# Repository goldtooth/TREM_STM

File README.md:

View this project on [CADLAB.io](https://cadlab.io/project/1897). 

# TREM_STM
dfgdfg

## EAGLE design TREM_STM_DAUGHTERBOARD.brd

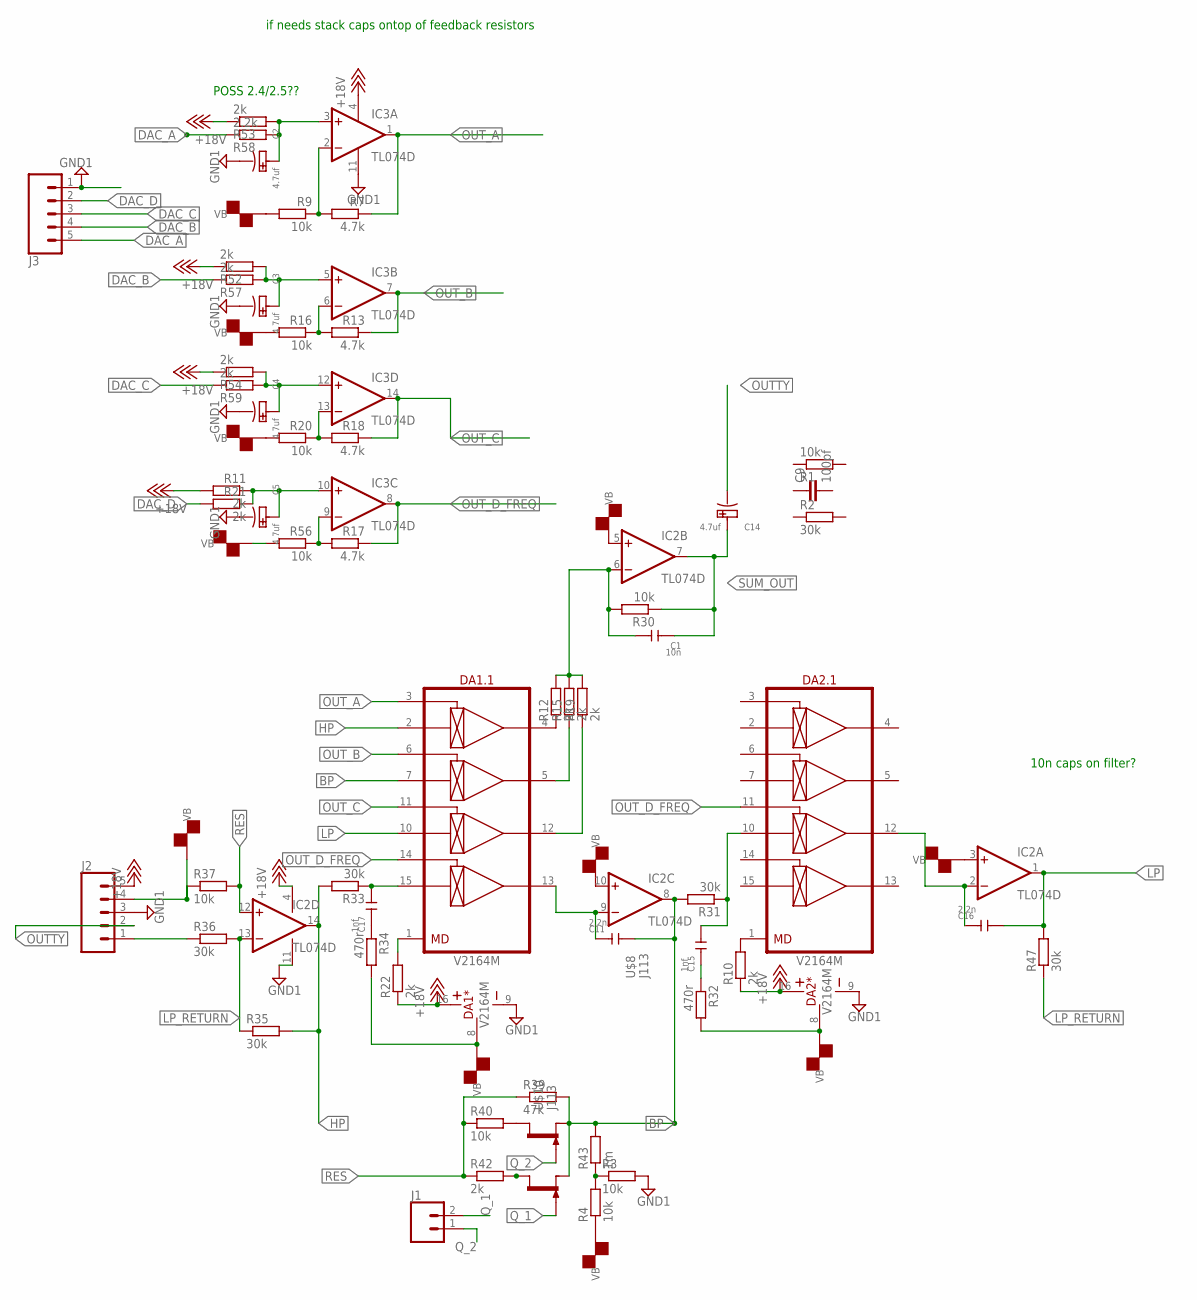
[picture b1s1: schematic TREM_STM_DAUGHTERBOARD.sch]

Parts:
C1: 10n; CERAMIC-5MM
C2, C3, C4, C5, C14: 4.7uf; PC-D5.3MM
C9: 100pf; C1206
C11, C16: 2.2n; CERAMIC-5MM
C15, C17: 1nf; CERAMIC-5MM
DA1, DA2: V2164M; SO-16
IC2, IC3: TL074D; SO14
J1: CONN_02PTH3; 1X02_LONGPADS
J2, J3: CONN_05PTH_LONGPADS; 1X05_LONGPADS
R1, R3, R4, R9, R16, R20, R30, R37, R40, R56: 10k; M1206
R2, R31, R33, R35, R36, R47: 30k; M1206
R7, R13, R17, R18: 4.7k; M1206
R10, R11, R12, R15, R19, R21, R22, R42, R52, R53, R54, R57, R59: 2k; M1206
R32, R34: 470r; M1206
R39: 47k; M1206
R43: 1m; M1206
R58: 2.2k; M1206
U$8, U$10: J113; TO92-

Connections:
+18V: DA1.16 (V+), DA2.16 (V+), IC2.4 (V+), IC3.4 (V+), J2.5, R10.1, R11.2, R22.1, R52.1, R53.1, R54.1
BP: C11.2, DA1.7 (IN2), IC2.8 (OUT), R31.2, R39.2, R43.2, U$8.2 (S), U$10.2 (S)
DAC_A: J3.5, R58.1
DAC_B: J3.4, R57.1
DAC_C: J3.3, R59.1
DAC_D: J3.2, R21.2
GND1: C2.-, C3.-, C4.-, C5.-, DA1.9 (V-), DA2.9 (V-), IC2.11 (V-), IC3.11 (V-), J2.3, J3.1, R3.2
HP: DA1.2 (IN1), IC2.14 (OUT), R33.2, R35.2
LP: C16.2, DA1.10 (IN3), IC2.1 (OUT), R47.2
LP_RETURN: IC2.13 (-IN), R35.1, R36.2, R47.1
unnamed: IC3.2 (-IN), R7.2, R9.1
unnamed: R3.1, R4.2, R43.1
unnamed: DA1.1 (MD), R22.2
unnamed: C2.+, IC3.3 (+IN), R53.2, R58.2
unnamed: C3.+, IC3.5 (+IN), R52.2, R57.2
unnamed: IC3.6 (-IN), R13.2, R16.1
unnamed: DA2.1 (MD), R10.2
unnamed: C4.+, IC3.12 (+IN), R54.2, R59.2
unnamed: C5.+, IC3.10 (+IN), R11.1, R21.1
unnamed: IC3.13 (-IN), R18.2, R20.1
unnamed: DA1.4 (OUT1), R12.1
unnamed: IC3.9 (-IN), R17.2, R56.1
unnamed: DA1.5 (OUT2), R15.1
unnamed: DA1.12 (OUT3), R19.1
unnamed: C1.2, IC2.6 (-IN), R12.2, R15.2, R19.2, R30.2
unnamed: J2.1, R36.1
unnamed: C11.1, DA1.13 (OUT4), IC2.9 (-IN)
unnamed: R40.2, U$10.3 (D)
unnamed: C15.2, DA2.10 (IN3), R31.1
unnamed: C15.1, R32.1
unnamed: C16.1, DA2.12 (OUT3), IC2.2 (-IN)
unnamed: R42.2, U$8.3 (D)
unnamed: C17.2, DA1.15 (IN4), R33.1
unnamed: C17.1, R34.1
OUTTY: C14.-, J2.2
OUT_A: DA1.3 (CV1), IC3.1 (OUT), R7.1
OUT_B: DA1.6 (CV2), IC3.7 (OUT), R13.1
OUT_C: DA1.11 (CV3), IC3.14 (OUT), R18.1
OUT_D_FREQ: DA1.14 (CV4), DA2.11 (CV3), IC3.8 (OUT), R17.1
Q_1: J1.2, U$8.1 (G)
Q_2: J1.1, U$10.1 (G)
RES: IC2.12 (+IN), R37.2, R39.1, R40.1, R42.1
SUM_OUT: C1.1, C14.+, IC2.7 (OUT), R30.1
VB: DA1.8 (GND), DA2.8 (GND), IC2.3 (+IN), IC2.5 (+IN), IC2.10 (+IN), J2.4, R4.1, R9.2, R16.2, R20.2, R32.2, R34.2, R37.1, R56.2

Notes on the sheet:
if needs stack caps ontop of feedback resistors
POSS 2.4/2.5??
10n caps on filter?

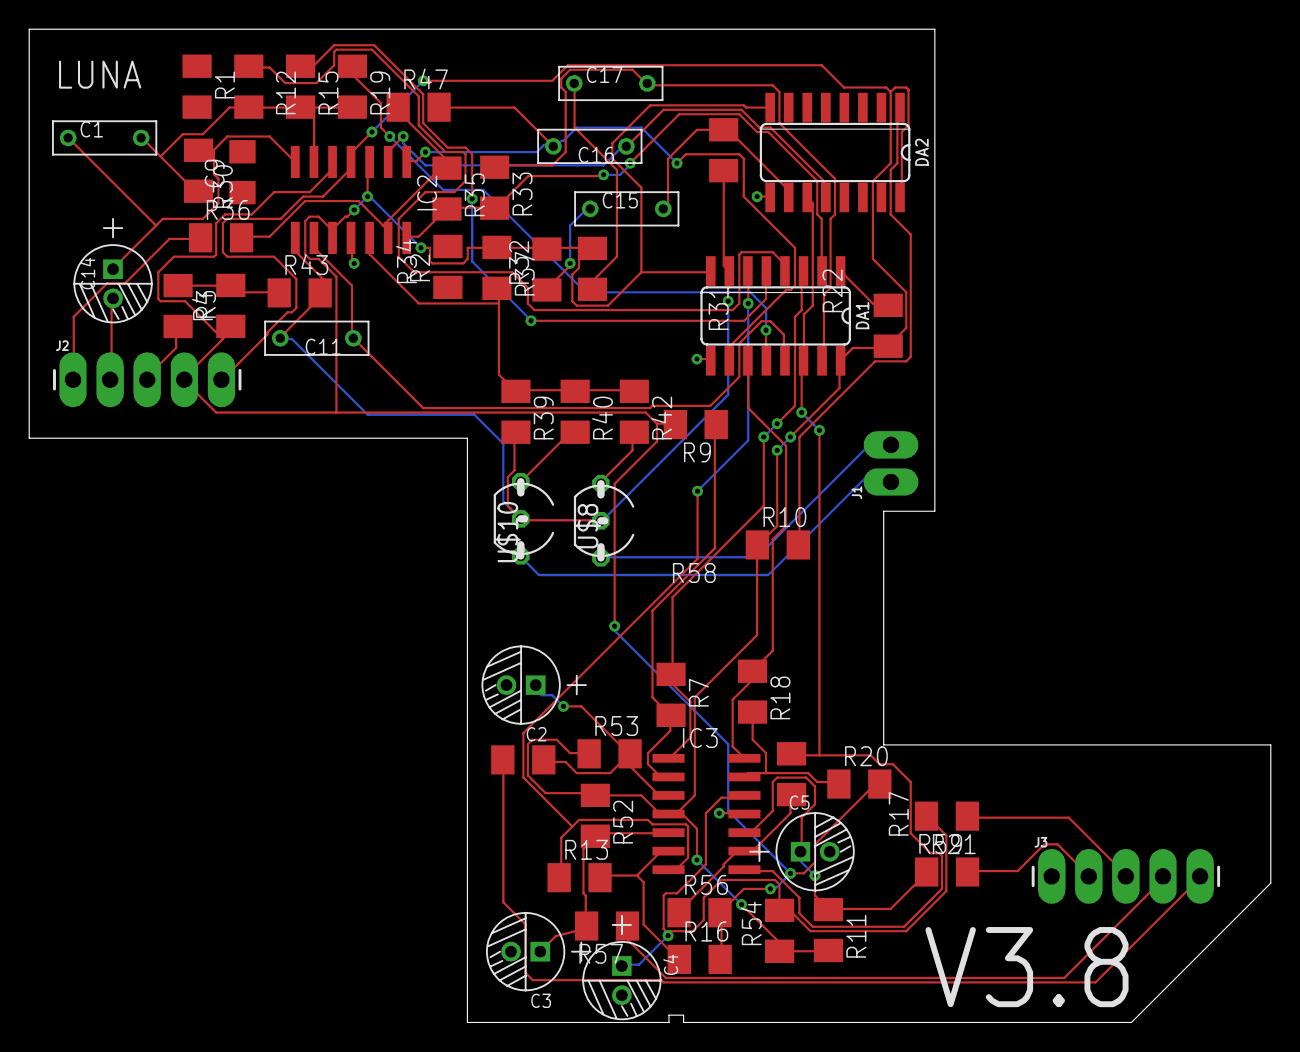
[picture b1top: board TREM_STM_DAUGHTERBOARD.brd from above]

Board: 2 copper layers, 85.0 x 68.0 mm, 58 parts (0 on the bottom side), 44 nets.

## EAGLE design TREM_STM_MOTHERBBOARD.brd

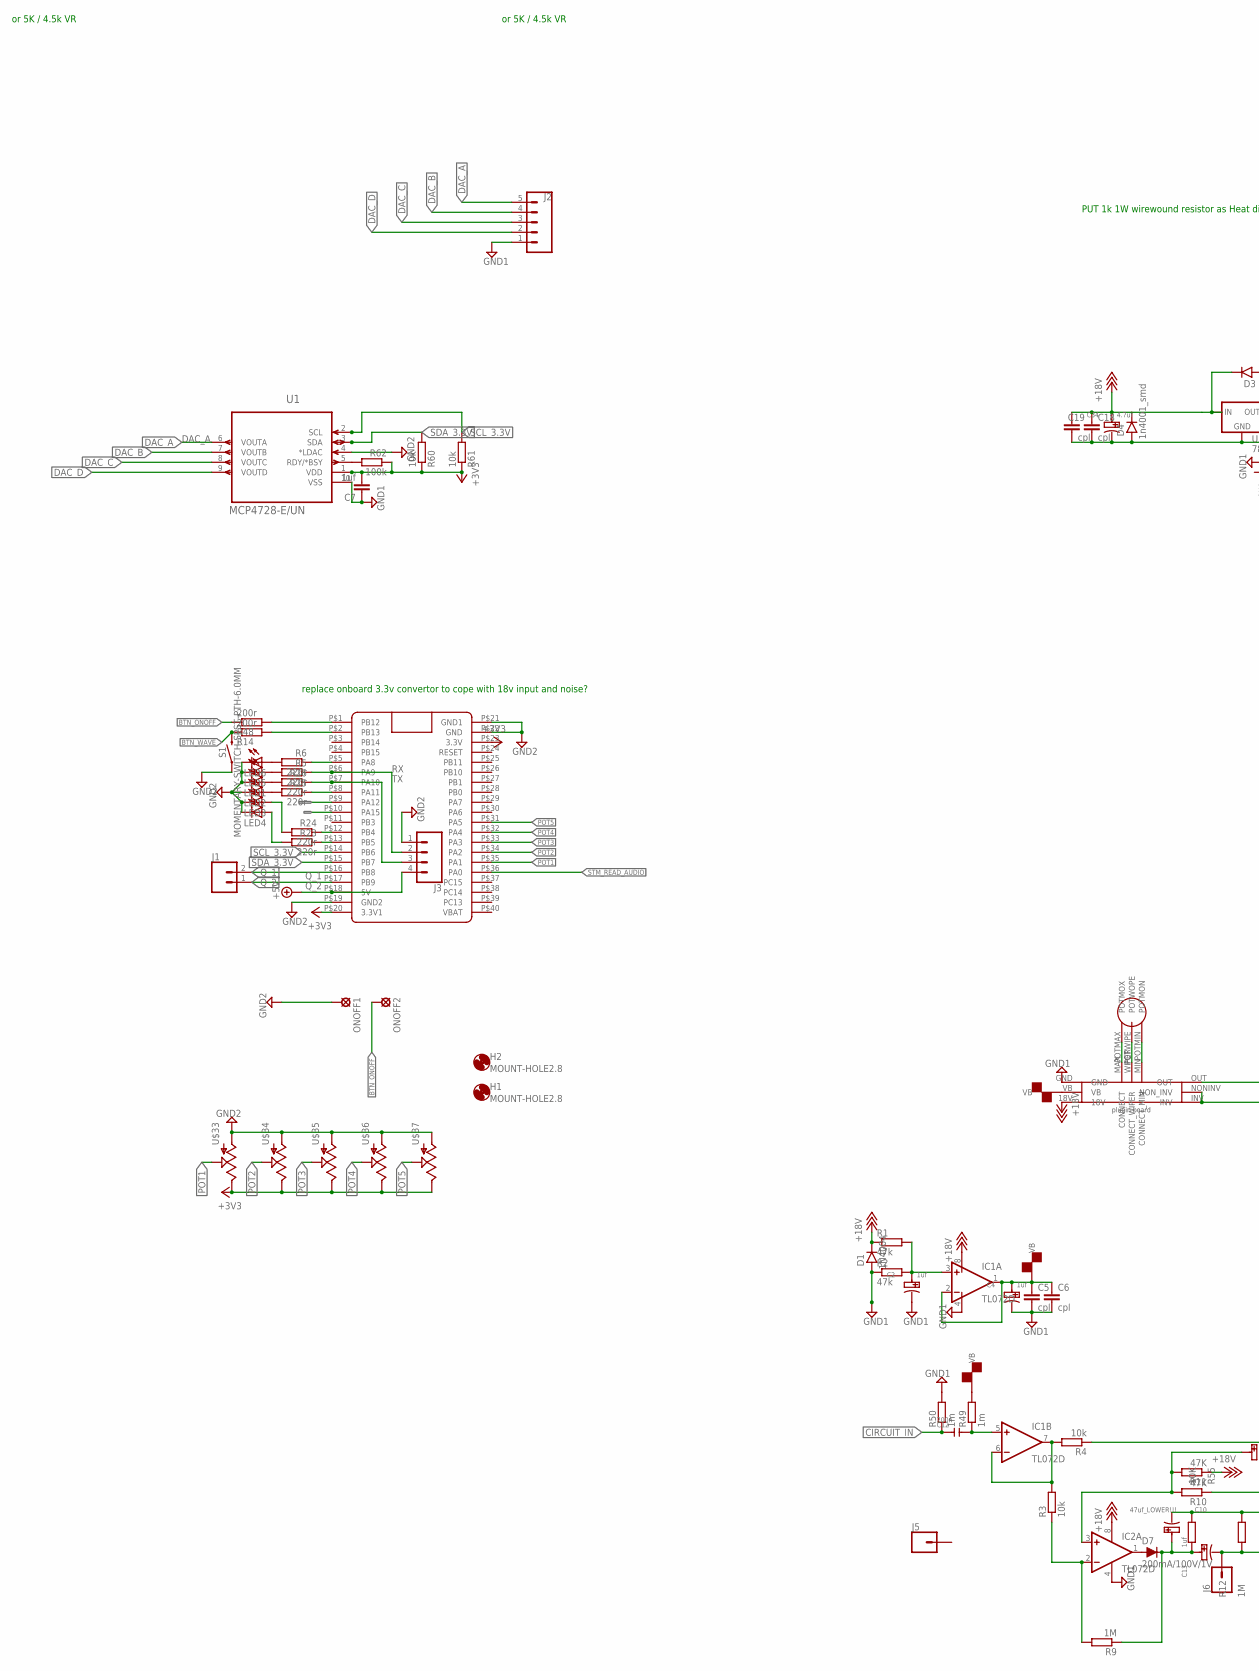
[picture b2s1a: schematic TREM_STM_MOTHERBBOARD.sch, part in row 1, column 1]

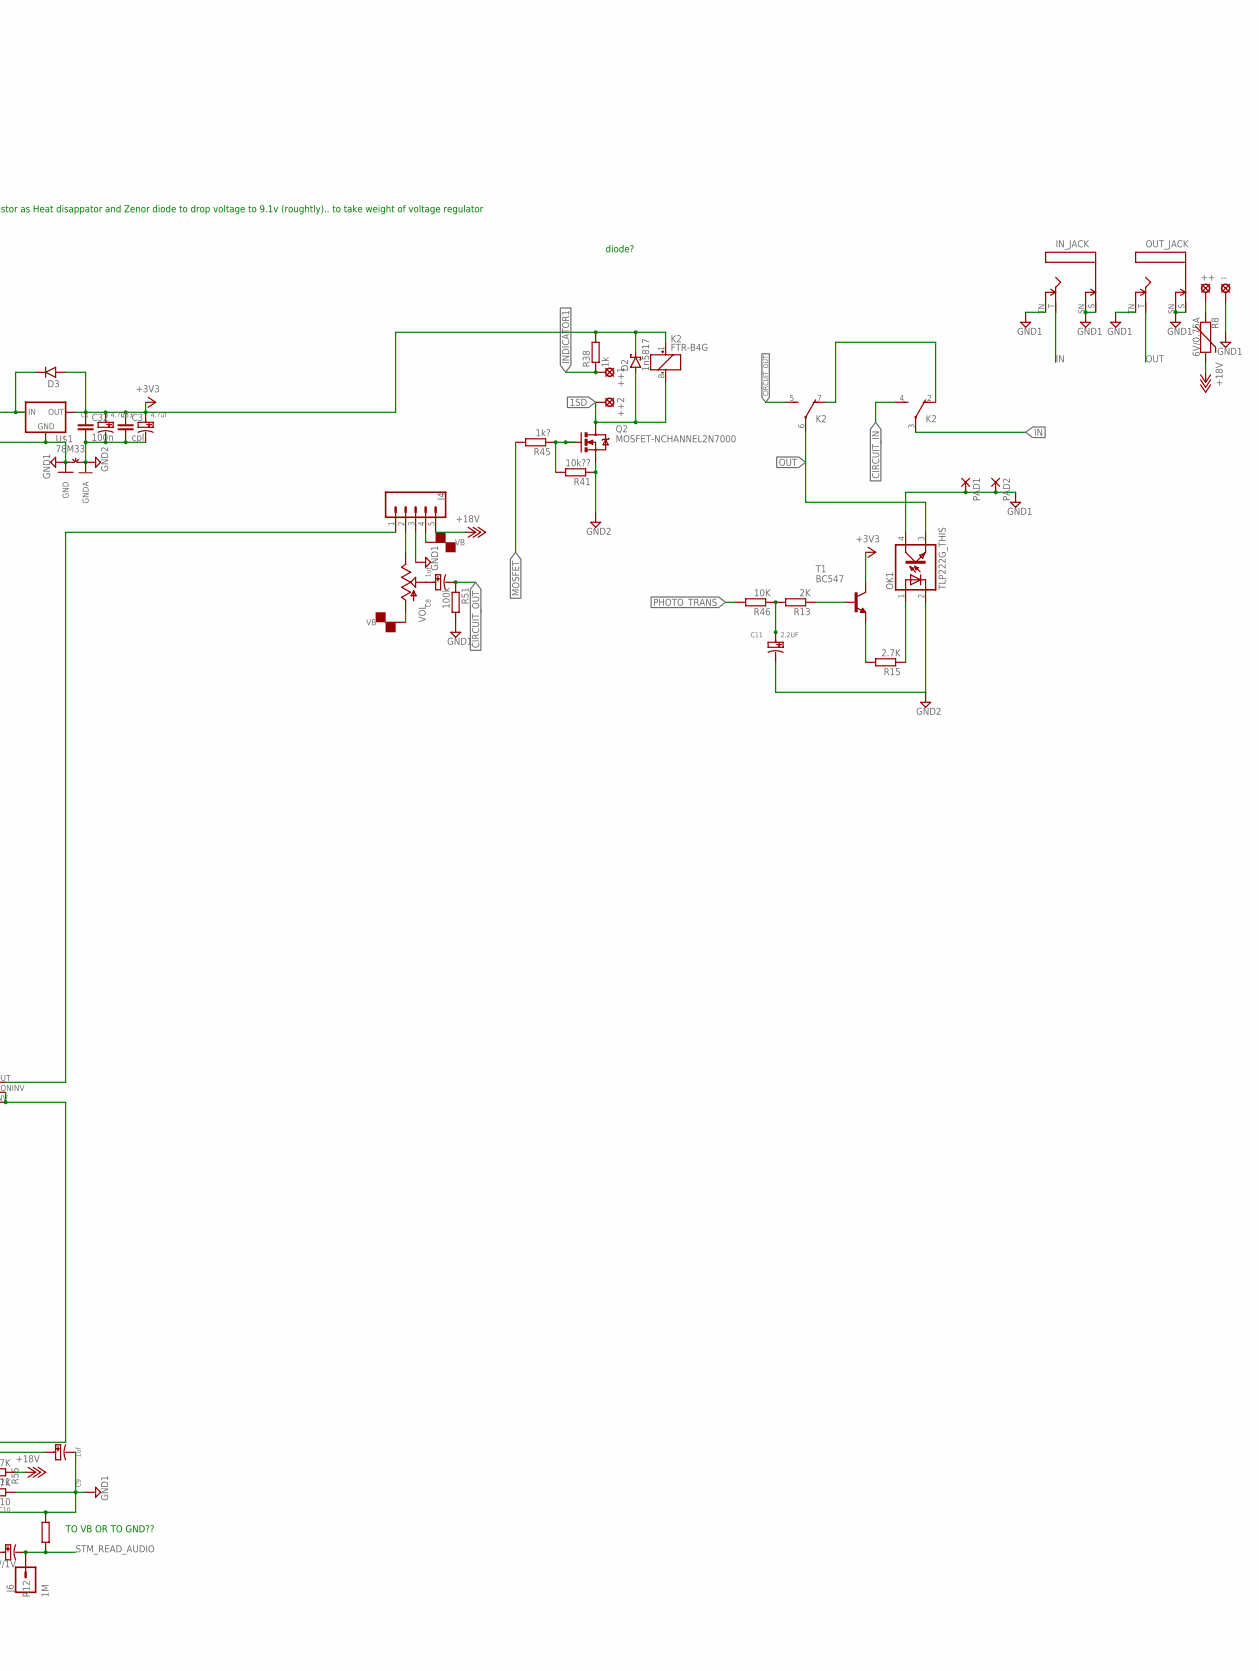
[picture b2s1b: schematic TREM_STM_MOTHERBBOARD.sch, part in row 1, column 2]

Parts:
++, ++1, ++2: LSP10
--: LSP10
C1, C33, C34: 4.7uf; PC-D5.3MM
C2, C4, C8, C9, C13: 1uf; PC-D5.3MM
C3, C5, C6, C18, C19: cpl; C1206
C7: 1uf; C1206
C10: 47uf_LOWER!!!; PC-D5.3MM
C11: 2.2UF; PC-D5.3MM
C12: 200n; CERAMIC-5MM
C32: 100n; C1206
D1: 1N4004; DO41-1
D2: 1n5817; SMB
D3, D4: 1n4001_smd; DO41-1
D7: 200mA/100V/1V; DIODE-1N4148
H1, H2: MOUNT-HOLE2.8; 2,8
IC1, IC2: TL072D; SO08
IN_JACK: MMMONNNNOHOLES; MONONOHOLES
J1: CONN_02PTH3; 1X02_LONGPADS
J2, J4: CONN_05PTH_LONGPADS; 1X05_LONGPADS
J3: CONN_04LONGPADS; 1X04_LONGPADS
J5, J6: CONN_01; 1X01
K2: FTR-B4G
LED1, LED2, LED3, LED4, LED5, LED6: LED3MM
OK1: TLP222G_THIS; DIL04
ONOFF1, ONOFF2: LSP10
OUT_JACK: MMMONNNNOHOLES; MONONOHOLES
PAD1, PAD2: SMD2; SMD1,27-2,54
Q2: MOSFET-NCHANNEL2N7000; TO-92
R1, R2: 47k; M1206
R3, R4, R60, R61: 10k; M1206
R5, R6, R23, R24, R25, R26: 220r; M1206
R8: 6V/0.75A; 1206
R9, R12: 1M; M1206
R10, R11: 47K; M1206
R13: 2K; M1206
R14, R48: 200r; M1206
R15: 2.7K; M1206
R38: 1k; M1206
R41: 10k??; M1206
R45: 1k?; M1206
R46, R55: 10K; M1206
R49, R50: 1m; M1206
R51, R62: 100k; M1206
S1: MOMENTARY-SWITCH-SPST-PTH-6.0MM; TACTILE_SWITCH_PTH_6.0MM
T1: BC547; TO92
U1: MCP4728-E/UN; SOP50P490X110-10N
U$1: 78M33; SOT223
U$4: GT_PLUGIN; PLUGIN_RECIEVE
U$11: BLUE_PILL
U$33, U$34, U$35, U$36, U$37: POT; ALPS_POT
VOL: POT; ALPS_POT
~NUDEV~1: GND-GNDA1,27MM; GND-GNDA-1,27MM

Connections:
1SD: ++2.MP, D2.A, K2.8 (-), Q2.3 (D)
+3V3: C1.+, C3.1, C7.2, C32.1, C33.+, D2.C, D3.A, K2.1 (+), R38.2, R60.1, R61.1, R62.1, T1.3 (C), U1.1 (VDD), U$1.3 (OUT), U$11.P$20 (3.3V1), U$11.P$23 (3.3V), U$33.P$1 (E), U$34.P$1 (E), U$35.P$1 (E), U$36.P$1 (E), U$37.P$1 (E)
+5V: J3.4, U$11.P$18 (5V)
+18V: D1.C, IC1.8 (V+), IC2.8 (V+), J4.5, R1.1, R8.2, R11.1, U$4.18V
BTN_ONOFF: ONOFF2.MP, R48.1
BTN_WAVE: R14.1, S1.3 (2)
CIRCUIT_IN: C12.1, K2.4 (S), R50.1
CIRCUIT_OUT: C8.-, K2.5 (S), R51.1
DAC_A: J2.5, U1.6 (VOUTA)
DAC_B: J2.4, U1.7 (VOUTB)
DAC_C: J2.3, U1.8 (VOUTC)
DAC_D: J2.2, U1.9 (VOUTD)
GND1: --.MP, C2.-, C4.-, C5.2, C6.2, C7.1, C9.-, C10.-, C18.2, C19.2, C34.-, D1.A, D4.A, IC1.4 (V-), IC2.4 (V-), IN_JACK.S, IN_JACK.SN, IN_JACK.TN, J2.1, J4.3, OK1.4 (COL), OUT_JACK.S, OUT_JACK.SN, OUT_JACK.TN, PAD1.1, PAD2.1, R2.1, R10.1, R12.2, R50.2, R51.2, R55.1, U1.10 (VSS), U$1.2 (GND), U$1.4 (GND), U$4.GND, ~NUDEV~1.GND
GND2: C1.-, C3.2, C11.-, C32.2, C33.-, J3.1, LED1.K (C), LED2.K (C), LED3.K (C), LED4.K (C), LED5.K (C), LED6.K (C), OK1.2 (C), ONOFF1.MP, Q2.1 (S), R41.1, S1.1, U1.4 (*LDAC), U$11.P$19 (GND2), U$11.P$21 (GND1), U$11.P$22 (GND), U$33.P$3 (A), U$34.P$3 (A), U$35.P$3 (A), U$36.P$3 (A), U$37.P$3 (A), ~NUDEV~1.GNDA
IN: IN_JACK.T, K2.3
INDICATOR1: ++1.MP, R38.1
MOSFET: R45.2, U$11.P$10 (PA15)
unnamed: J4.1, U$4.OUT
unnamed: C2.+, IC1.3 (+IN), R1.2, R2.2
unnamed: U$4.MAX (CONNECT), U$4.POTMAX (POTMOX)
unnamed: U$4.POTWIPE (POTWOPE), U$4.WIPER (CONNECT_WIPER)
unnamed: U$4.MIN (CONNECT_MIN), U$4.POTMIN (POTMON)
unnamed: R4.1, U$4.INV, U$4.NONINV (NON_INV)
unnamed: R23.1, U$11.P$13 (PB5)
unnamed: R24.1, U$11.P$12 (PB4)
unnamed: C9.+, IC2.3 (+IN), R10.2, R11.2
unnamed: C8.+, VOL.P$2 (S)
unnamed: C18.1, C19.1, C34.+, D3.C, D4.C, U$1.1 (IN)
unnamed: R62.2, U1.5 (RDY/*BSY)
unnamed: C10.+, C13.+, D7.C, R9.1, R55.2
unnamed: IC2.2 (-IN), R3.1, R9.2
unnamed: C11.+, R13.2, R46.1
unnamed: IC1.6 (-IN), IC1.7 (OUT), R3.2, R4.2
unnamed: D7.A, IC2.1 (OUT)
unnamed: R15.2, T1.1 (E)
unnamed: R25.1, U$11.P$8 (PA11)
unnamed: OK1.1 (A), R15.1
unnamed: R13.1, T1.2 (B)
unnamed: LED1.A, R26.2
unnamed: LED2.A, R25.2
unnamed: K2.2 (O), K2.7 (O)
unnamed: LED3.A, R24.2
unnamed: LED4.A, R23.2
unnamed: J4.2, VOL.P$1 (E)
unnamed: ++.MP, R8.1
unnamed: C12.2, IC1.5 (+IN), R49.1
unnamed: R48.2, U$11.P$1 (PB12)
unnamed: R14.2, U$11.P$2 (PB13)
unnamed: R6.1, U$11.P$5 (PA8)
unnamed: LED5.A, R5.2
unnamed: LED6.A, R6.2
unnamed: Q2.2 (G), R41.2, R45.1
OUT: K2.6, OK1.3 (EMIT), OUT_JACK.T
PHOTO_TRANS: R46.2, U$11.P$9 (PA12)
POT1: U$11.P$35 (PA1), U$33.P$2 (S)
POT2: U$11.P$34 (PA2), U$34.P$2 (S)
POT3: U$11.P$33 (PA3), U$35.P$2 (S)
POT4: U$11.P$32 (PA4), U$36.P$2 (S)
POT5: U$11.P$31 (PA5), U$37.P$2 (S)
Q_1: J1.2, U$11.P$16 (PB8)
Q_2: J1.1, U$11.P$17 (PB9)
RX: J3.2, R5.1, U$11.P$6 (PA9)
SCL_3.3V: R61.2, U1.2 (SCL), U$11.P$14 (PB6)
SDA_3.3V: R60.2, U1.3 (SDA), U$11.P$15 (PB7)
STM_READ_AUDIO: C13.-, J6.1, R12.1, U$11.P$36 (PA0)
TX: J3.3, R26.1, U$11.P$7 (PA10)
VB: C4.+, C5.1, C6.1, IC1.1 (OUT), IC1.2 (-IN), J4.4, R49.2, U$4.VB, VOL.P$3 (A)

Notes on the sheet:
diode?
replace onboard 3.3v convertor to cope with 18v input and noise?
or 5K / 4.5k VR
PUT 1k 1W wirewound resistor as Heat disappator and Zenor diode to drop voltage to 9.1v (roughtly).. to take weight of voltage regulator
TO VB OR TO GND??

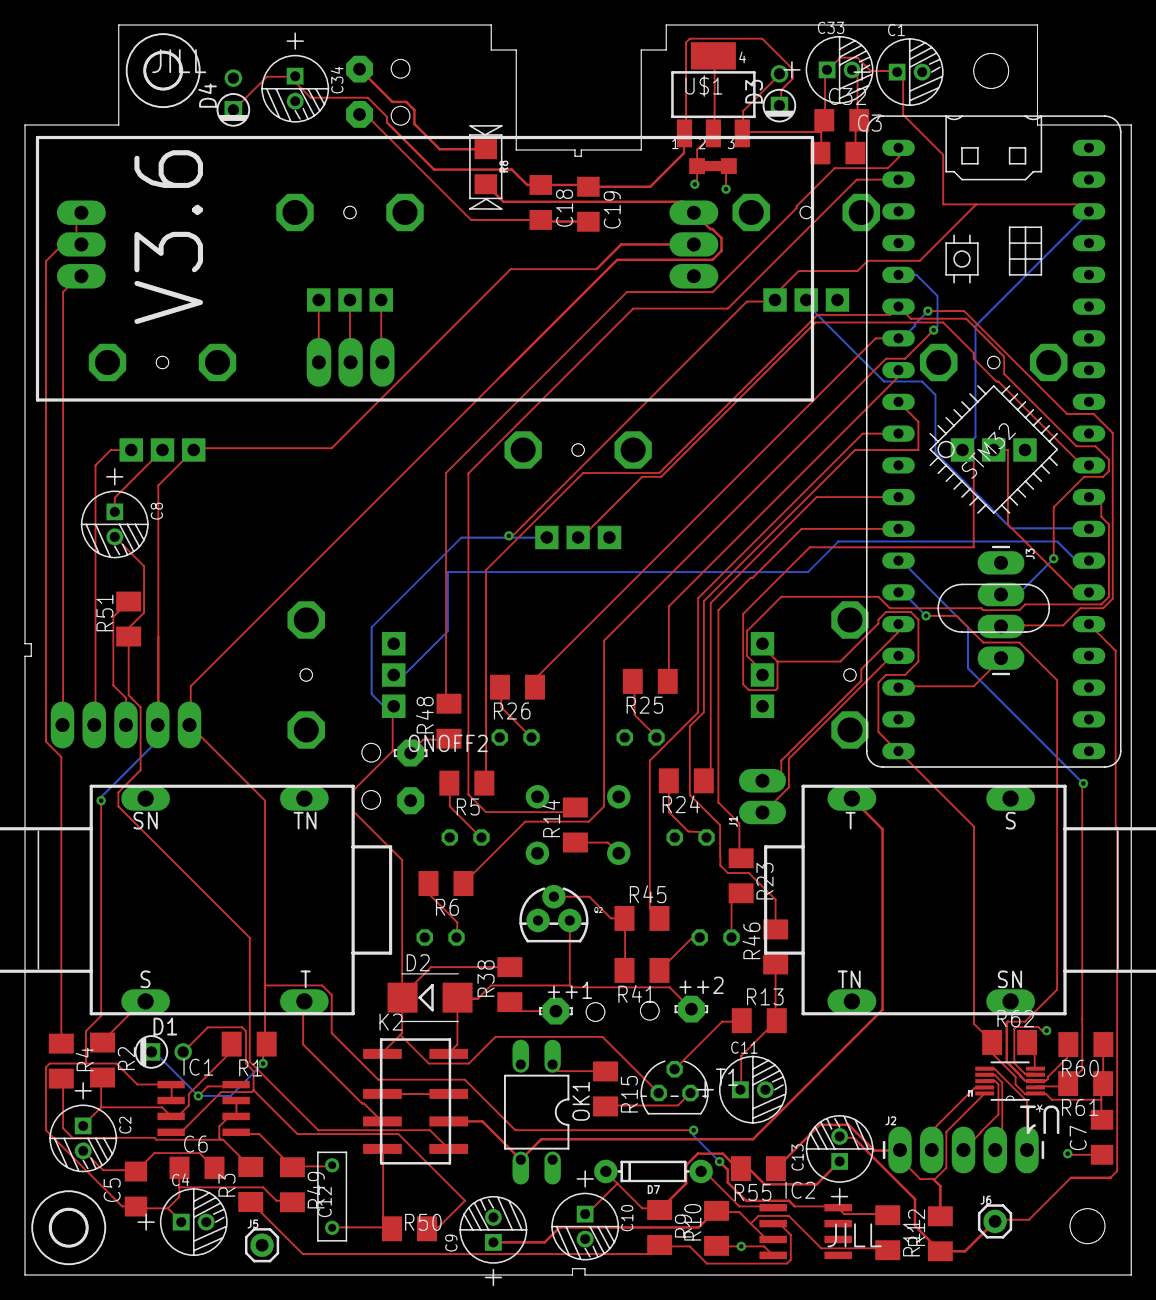
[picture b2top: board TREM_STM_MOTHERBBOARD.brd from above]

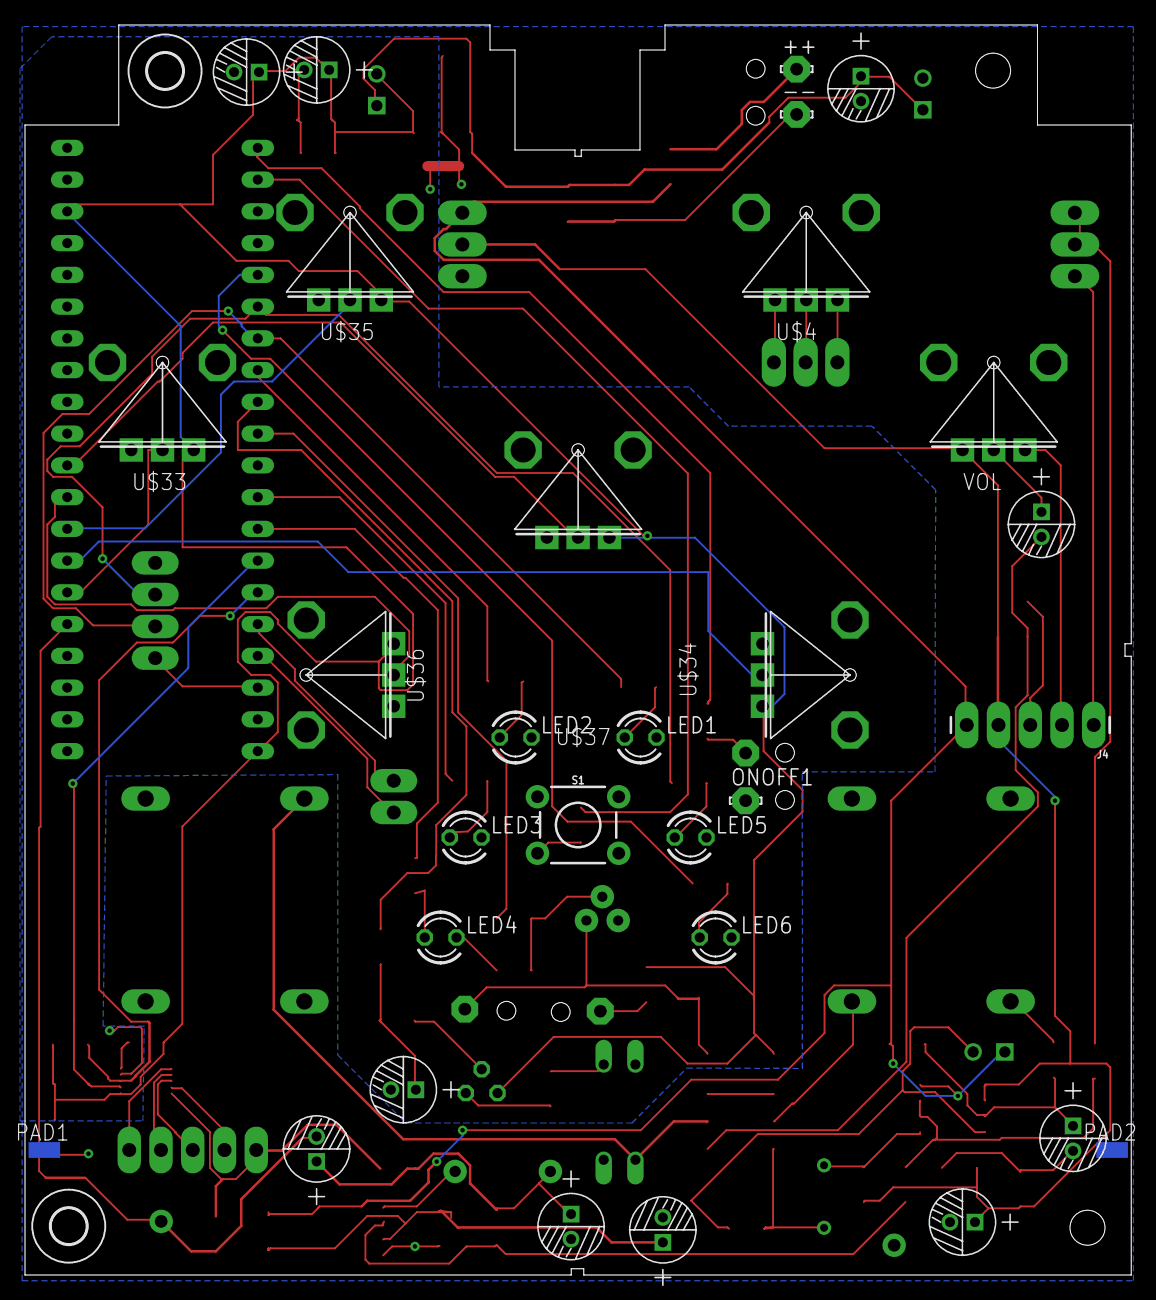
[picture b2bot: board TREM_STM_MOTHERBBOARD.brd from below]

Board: 2 copper layers, 88.5 x 100.0 mm, 103 parts (15 on the bottom side), 67 nets.

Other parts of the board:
H3, H4: MOUNT-HOLE2.8; 2,8
U$2, U$3, U$5, U$9, U$12, U$13: HOLD

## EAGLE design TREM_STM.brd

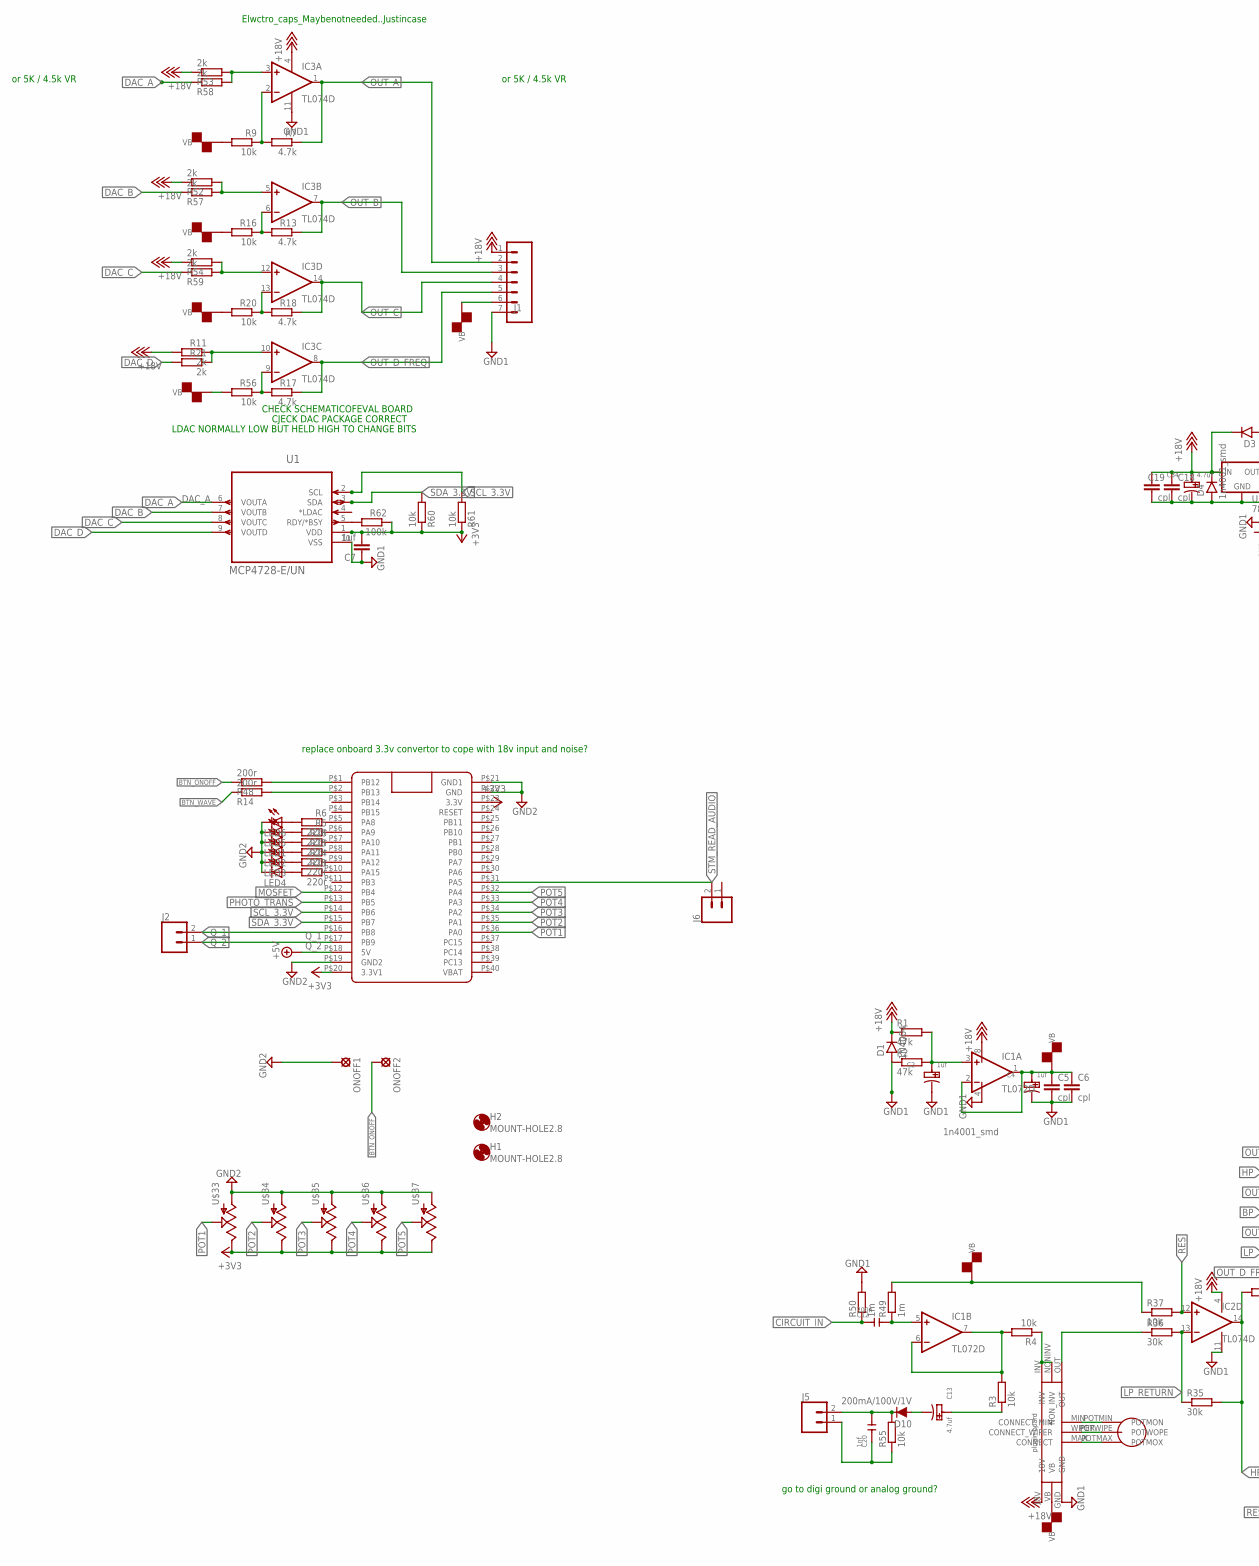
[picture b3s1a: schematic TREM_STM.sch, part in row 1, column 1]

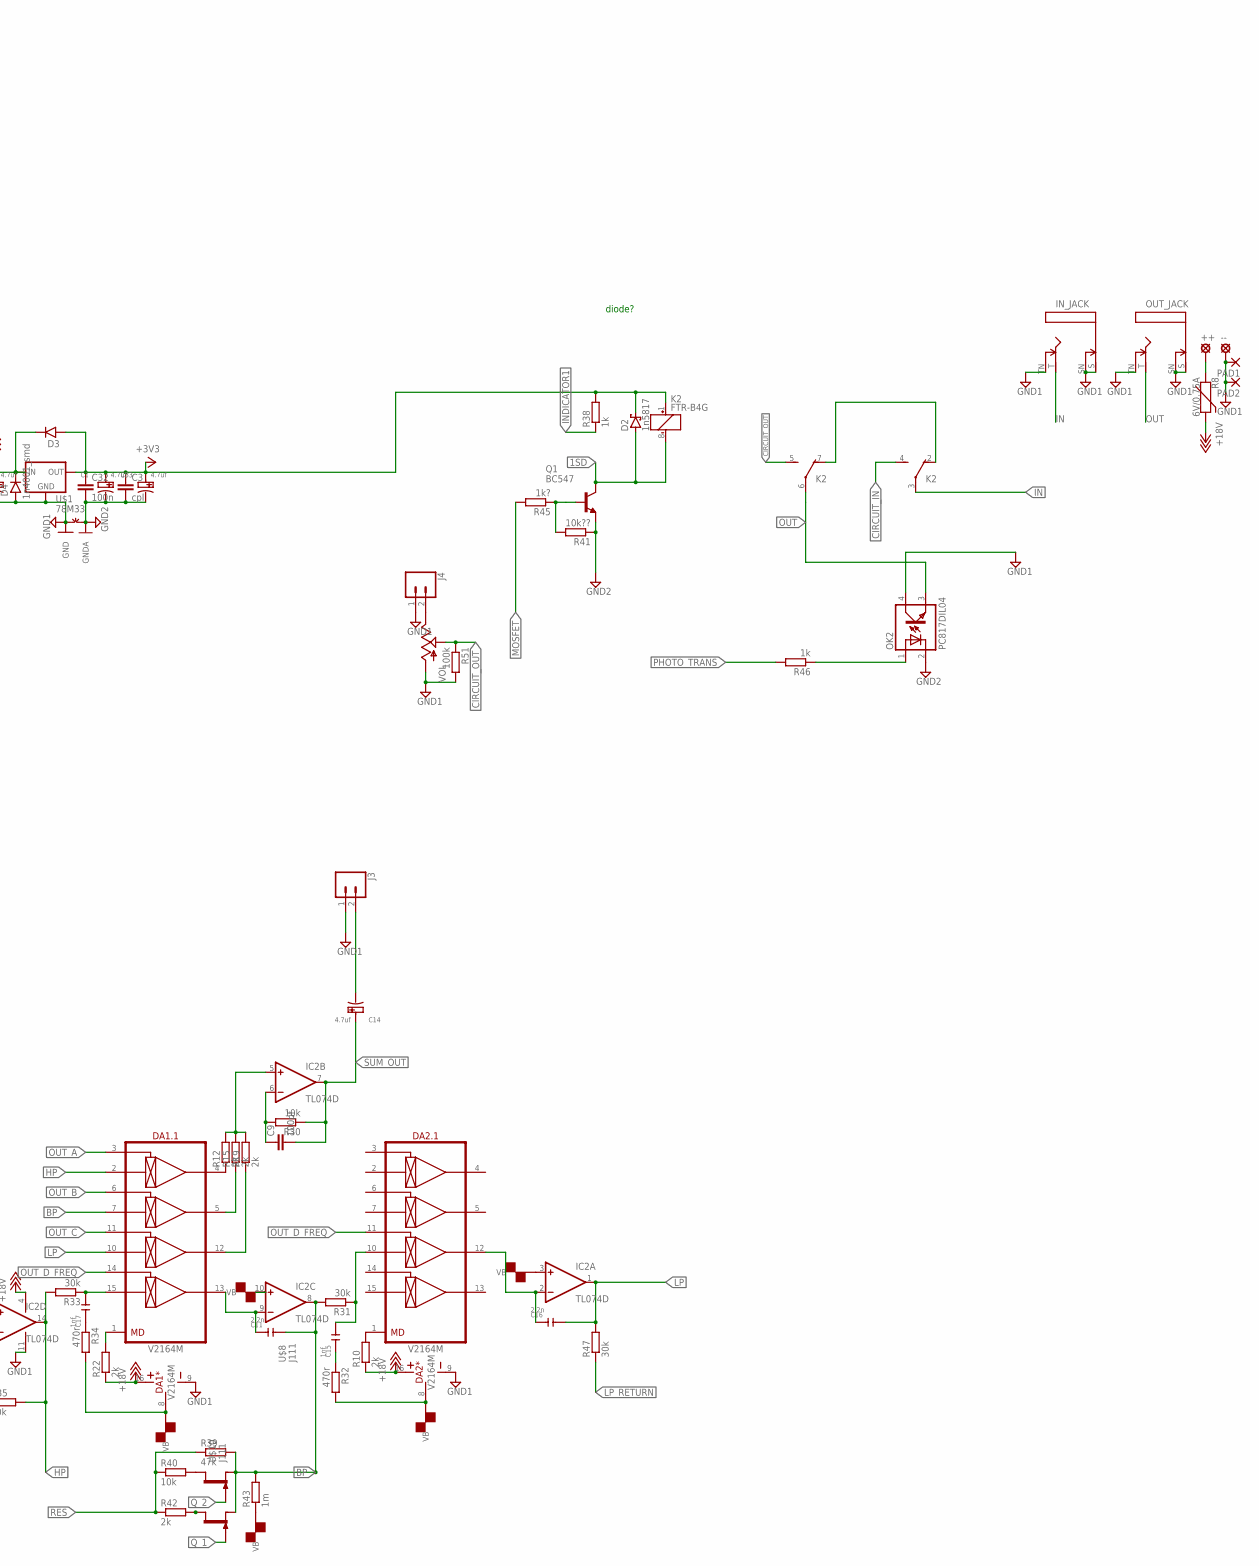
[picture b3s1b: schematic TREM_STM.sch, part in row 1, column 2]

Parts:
++: LSP10
--: LSP10
C1, C13, C14, C33, C34: 4.7uf; PC-D5.3MM
C2, C4: 1uf; PC-D5.3MM
C3, C5, C6, C18, C19: cpl; C1206
C7: 1uf; C1206
C9: 100pf; C1206
C11, C16: 2.2n; CERAMIC-5MM
C12: 200n; CERAMIC-5MM
C15, C17, C20: 1nf; CERAMIC-5MM
C32: 100n; C1206
D1: 1N4004; DO41-1
D2: 1n5817; SMB
D3, D4: 1n4001_smd; DO41-1
D10: 200mA/100V/1V; DIODE-1N4148
DA1, DA2: V2164M; SO-16
H1, H2: MOUNT-HOLE2.8; 2,8
IC1: TL072D; SO08
IC2, IC3: TL074D; SO14
IN_JACK: MMMONNNNOHOLES; MONONOHOLES
J1: CONN_07LONGPADS; 1X07_LONGPADS
J2, J3, J4, J5, J6: CONN_02PTH3; 1X02_LONGPADS
K2: FTR-B4G
LED1, LED2, LED3, LED4, LED5, LED6: LED3MM
OK2: PC817DIL04; SMD4
ONOFF1, ONOFF2: LSP10
OUT_JACK: MMMONNNNOHOLES; MONONOHOLES
PAD1, PAD2: SMD5; SMD2,54-5,08
Q1: BC547; TO92
R1, R2, R39: 47k; M1206
R3, R4, R9, R16, R20, R30, R37, R40, R55, R56, R60, R61: 10k; M1206
R5, R6, R23, R24, R25, R26: 220r; M1206
R7, R13, R17, R18: 4.7k; M1206
R8: 6V/0.75A; 1206
R10, R11, R12, R15, R19, R21, R22, R42, R52, R53, R54, R57, R58, R59: 2k; M1206
R14, R48: 200r; M1206
R31, R33, R35, R36, R47: 30k; M1206
R32, R34: 470r; M1206
R38, R46: 1k; M1206
R41: 10k??; M1206
R43, R49, R50: 1m; M1206
R45: 1k?; M1206
R51, R62: 100k; M1206
U1: MCP4728-E/UN; SOP50P490X110-10N
U$1: 78M33; SOT223
U$8, U$10: J111; TO92-
U$11: BLUE_PILL
U$32: GT_PLUGIN; PLUGIN_RECIEVE
U$33, U$34, U$35, U$36, U$37: POT; ALPS_POT
VOL: POT; ALPS_POT
~NUDEV~1: GND-GNDA1,27MM; GND-GNDA-1,27MM

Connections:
1SD: D2.A, K2.8 (-), Q1.3 (C)
+3V3: C1.+, C3.1, C7.2, C32.1, C33.+, D2.C, D3.A, K2.1 (+), R38.2, R60.1, R61.1, R62.1, U1.1 (VDD), U$1.3 (OUT), U$11.P$20 (3.3V1), U$11.P$23 (3.3V), U$33.P$1 (E), U$34.P$1 (E), U$35.P$1 (E), U$36.P$1 (E), U$37.P$1 (E)
+5V: U$11.P$18 (5V)
+18V: C18.1, C19.1, C34.+, D1.C, D3.C, D4.C, DA1.16 (V+), DA2.16 (V+), IC1.8 (V+), IC2.4 (V+), IC3.4 (V+), J1.1, R1.1, R8.2, R10.1, R11.2, R22.1, R52.1, R53.1, R54.1, U$1.1 (IN), U$32.18V
BP: C11.2, DA1.7 (IN2), IC2.8 (OUT), R31.2, R39.2, R43.2, U$8.2 (S), U$10.2 (S)
BTN_ONOFF: ONOFF2.MP, R48.1
BTN_WAVE: R14.1
CIRCUIT_IN: C12.1, K2.4 (S), R50.1
CIRCUIT_OUT: K2.5 (S), R51.1, VOL.P$2 (S)
DAC_A: R58.1, U1.6 (VOUTA)
DAC_B: R57.1, U1.7 (VOUTB)
DAC_C: R59.1, U1.8 (VOUTC)
DAC_D: R21.2, U1.9 (VOUTD)
GND1: --.MP, C2.-, C4.-, C5.2, C6.2, C7.1, C18.2, C19.2, C34.-, D1.A, D4.A, DA1.9 (V-), DA2.9 (V-), IC1.4 (V-), IC2.11 (V-), IC3.11 (V-), IN_JACK.S, IN_JACK.SN, IN_JACK.TN, J1.7, J3.1, J4.1, OK2.4 (COL), OUT_JACK.S, OUT_JACK.SN, OUT_JACK.TN, PAD1.1, PAD2.1, R2.1, R50.2, U1.10 (VSS), U$1.2 (GND), U$1.4 (GND), U$32.GND, ~NUDEV~1.GND
GND2: C1.-, C3.2, C32.2, C33.-, LED1.K (C), LED2.K (C), LED3.K (C), LED4.K (C), LED5.K (C), LED6.K (C), OK2.2 (C), ONOFF1.MP, Q1.1 (E), R41.1, U$11.P$19 (GND2), U$11.P$21 (GND1), U$11.P$22 (GND), U$33.P$3 (A), U$34.P$3 (A), U$35.P$3 (A), U$36.P$3 (A), U$37.P$3 (A), ~NUDEV~1.GNDA
HP: DA1.2 (IN1), IC2.14 (OUT), R33.2, R35.2
IN: IN_JACK.T, K2.3
INDICATOR1: R38.1
LP: C16.2, DA1.10 (IN3), IC2.1 (OUT), R47.2
LP_RETURN: IC2.13 (-IN), R35.1, R36.2, R47.1
MOSFET: R45.2, U$11.P$12 (PB4)
unnamed: IC3.2 (-IN), R7.2, R9.1
unnamed: C2.+, IC1.3 (+IN), R1.2, R2.2
unnamed: DA1.1 (MD), R22.2
unnamed: IC3.3 (+IN), R53.2, R58.2
unnamed: IC3.5 (+IN), R52.2, R57.2
unnamed: IC3.6 (-IN), R13.2, R16.1
unnamed: DA2.1 (MD), R10.2
unnamed: IC3.12 (+IN), R54.2, R59.2
unnamed: IC3.10 (+IN), R11.1, R21.1
unnamed: IC3.13 (-IN), R18.2, R20.1
unnamed: DA1.4 (OUT1), R12.1
unnamed: R62.2, U1.5 (RDY/*BSY)
unnamed: IC3.9 (-IN), R17.2, R56.1
unnamed: DA1.5 (OUT2), R15.1
unnamed: DA1.12 (OUT3), R19.1
unnamed: IC1.6 (-IN), IC1.7 (OUT), R3.2, R4.2
unnamed: R23.1, U$11.P$10 (PA15)
unnamed: R24.1, U$11.P$9 (PA12)
unnamed: R25.1, U$11.P$8 (PA11)
unnamed: IC2.5 (+IN), R12.2, R15.2, R19.2
unnamed: C9.1, IC2.6 (-IN), R30.2
unnamed: R26.1, U$11.P$7 (PA10)
unnamed: R36.1, U$32.OUT
unnamed: C11.1, DA1.13 (OUT4), IC2.9 (-IN)
unnamed: R40.2, U$10.3 (D)
unnamed: C15.2, DA2.10 (IN3), R31.1
unnamed: C15.1, R32.1
unnamed: C16.1, DA2.12 (OUT3), IC2.2 (-IN)
unnamed: R42.2, U$8.3 (D)
unnamed: C17.2, DA1.15 (IN4), R33.1
unnamed: LED1.A, R26.2
unnamed: R4.1, U$32.INV, U$32.NONINV (NON_INV)
unnamed: U$32.MIN (CONNECT_MIN), U$32.POTMIN (POTMON)
unnamed: U$32.POTWIPE (POTWOPE), U$32.WIPER (CONNECT_WIPER)
unnamed: U$32.MAX (CONNECT), U$32.POTMAX (POTMOX)
unnamed: LED2.A, R25.2
unnamed: K2.2 (O), K2.7 (O)
unnamed: LED3.A, R24.2
unnamed: LED4.A, R23.2
unnamed: J4.2, VOL.P$1 (E)
unnamed: ++.MP, R8.1
unnamed: C17.1, R34.1
unnamed: C12.2, IC1.5 (+IN), R49.1
unnamed: C13.-, D10.A
unnamed: R51.2, VOL.P$3 (A)
unnamed: C13.+, R3.1
unnamed: R48.2, U$11.P$1 (PB12)
unnamed: R14.2, U$11.P$2 (PB13)
unnamed: R5.1, U$11.P$6 (PA9)
unnamed: R6.1, U$11.P$5 (PA8)
unnamed: LED5.A, R5.2
unnamed: LED6.A, R6.2
unnamed: C20.1, J5.1, R55.1
unnamed: Q1.2 (B), R41.2, R45.1
unnamed: OK2.1 (A), R46.1
OUT: K2.6, OK2.3 (EMIT), OUT_JACK.T
OUT_A: DA1.3 (CV1), IC3.1 (OUT), J1.2, R7.1
OUT_B: DA1.6 (CV2), IC3.7 (OUT), J1.3, R13.1
OUT_C: DA1.11 (CV3), IC3.14 (OUT), J1.4, R18.1
OUT_D_FREQ: DA1.14 (CV4), DA2.11 (CV3), IC3.8 (OUT), J1.5, R17.1
PHOTO_TRANS: R46.2, U$11.P$13 (PB5)
POT1: U$11.P$36 (PA0), U$33.P$2 (S)
POT2: U$11.P$35 (PA1), U$34.P$2 (S)
POT3: U$11.P$34 (PA2), U$35.P$2 (S)
POT4: U$11.P$33 (PA3), U$36.P$2 (S)
POT5: U$11.P$32 (PA4), U$37.P$2 (S)
Q_1: J2.2, U$8.1 (G), U$11.P$16 (PB8)
Q_2: J2.1, U$10.1 (G), U$11.P$17 (PB9)
READ: C14.-, J3.2
RES: IC2.12 (+IN), R37.2, R39.1, R40.1, R42.1
SCL_3.3V: R61.2, U1.2 (SCL), U$11.P$14 (PB6)
SDA_3.3V: R60.2, U1.3 (SDA), U$11.P$15 (PB7)
STM_READ_AUDIO: C20.2, D10.C, J5.2, J6.2, R55.2, U$11.P$31 (PA5)
SUM_OUT: C9.2, C14.+, IC2.7 (OUT), R30.1
VB: C4.+, C5.1, C6.1, DA1.8 (GND), DA2.8 (GND), IC1.1 (OUT), IC1.2 (-IN), IC2.3 (+IN), IC2.10 (+IN), J1.6, R9.2, R16.2, R20.2, R32.2, R34.2, R37.1, R43.1, R49.2, R56.2, U$32.VB

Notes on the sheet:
diode?
CHECK SCHEMATICOFEVAL BOARD
Elwctro_caps_Maybenotneeded..Justincase
CJECK DAC PACKAGE CORRECT
replace onboard 3.3v convertor to cope with 18v input and noise?
or 5K / 4.5k VR
LDAC NORMALLY LOW BUT HELD HIGH TO CHANGE BITS
go to digi ground or analog ground?

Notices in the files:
parts and their libraries:
SparkFun-DiscreteSemi: Licensing: Creative Commons ShareAlike 4.0 International - https://creativecommons.org/licenses/by-sa/4.0
